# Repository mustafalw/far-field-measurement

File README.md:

# far-field-measurement
This is our EE344 - Electronics Design Lab (EDL) project to build an apparatus for far field measurement of optical sources

A physical apparatus has been designed (a couple of pictures of the same are also there in the repository) to measure the far field angular radiation profile of optical sources like LEDs and laser diodes. The repository contains the comprehensive report, presentation, PCB designs, SPICE designs, LabVIEW codes and the final measurements. In addition, the video demonstrating the working of the apparatus can be found here: https://drive.google.com/open?id=0BwXnf3wcw68YSDE1a096Rm54bTg

Thanks!

Mustafa, Jashan and Deepak

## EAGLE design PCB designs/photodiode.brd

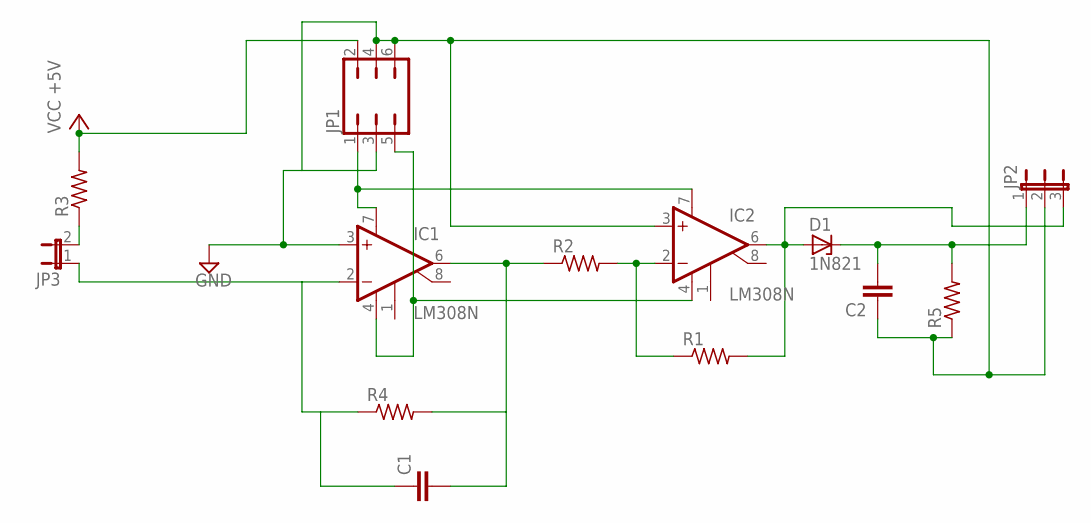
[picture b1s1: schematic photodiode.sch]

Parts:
C1, C2: C-EU025-024X044; C025-024X044
D1: 1N821; DO35Z10
IC1, IC2: LM308N; DIL08
JP1: JP3Q
JP2: JP2E; JP2
JP3: JP1E; JP1
R1, R2, R3, R4, R5: R-US_0207/10; 0207/10

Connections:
GND: C2.1, IC1.3 (+IN), IC2.3 (+IN), JP1.3, JP1.4, JP1.6, JP2.2, R5.1
unnamed: JP3.2, R3.1
unnamed: C1.1, IC1.2 (-IN), JP3.1, R4.1
unnamed: C1.2, IC1.6 (OUT), R2.1, R4.2
unnamed: IC1.7 (V+), IC2.7 (V+), JP1.1
unnamed: D1.A, IC2.6 (OUT), JP2.3, R1.2
unnamed: IC1.4 (V-), IC2.4 (V-), JP1.5
unnamed: C2.2, D1.C, JP2.1, R5.2
unnamed: IC2.2 (-IN), R1.1, R2.2
VCC: JP1.2, R3.2

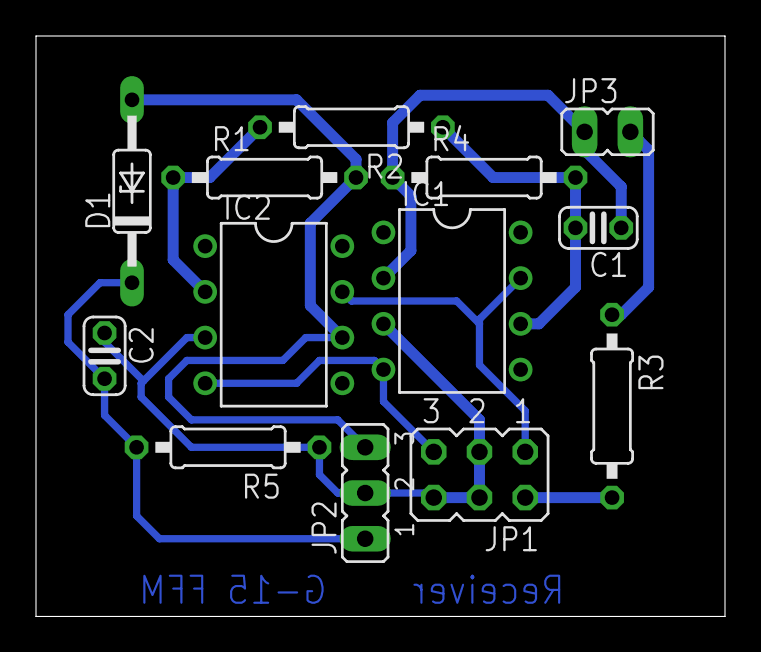
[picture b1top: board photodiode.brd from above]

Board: 2 copper layers, 38.3 x 32.2 mm, 13 parts (0 on the bottom side), 10 nets.

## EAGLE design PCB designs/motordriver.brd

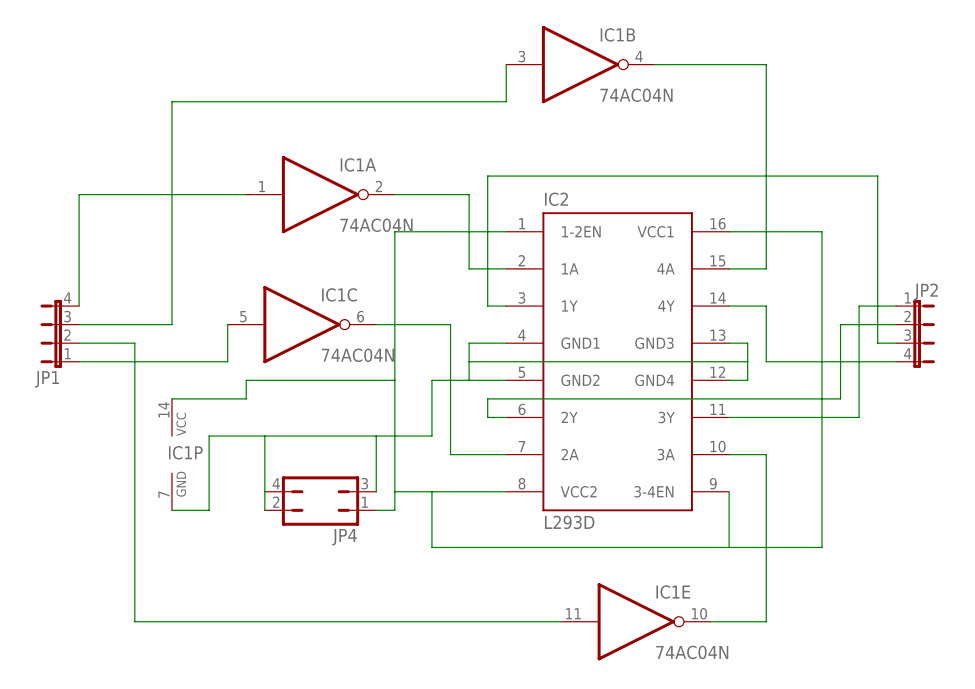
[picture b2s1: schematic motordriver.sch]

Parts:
IC1: 74AC04N; DIL14
IC2: L293D; DIL16
JP1, JP2: JP4E; JP4
JP4: JP2Q

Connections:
unnamed: IC1.1 (I), JP1.4
unnamed: IC1.5 (I), JP1.1
unnamed: IC1.3 (I), JP1.3
unnamed: IC1.2 (O), IC2.2 (1A)
unnamed: IC1.6 (O), IC2.7 (2A)
unnamed: IC1.4 (O), IC2.15 (4A)
unnamed: IC1.10 (O), IC2.10 (3A)
unnamed: IC2.3 (1Y), JP2.3
unnamed: IC2.6 (2Y), JP2.2
unnamed: IC2.11 (3Y), JP2.1
unnamed: IC2.14 (4Y), JP2.4
unnamed: IC1.11 (I), JP1.2
unnamed: IC1.14 (VCC), IC2.1 (1-2EN), IC2.8 (VCC2), IC2.9 (3-4EN), IC2.16 (VCC1), JP4.1
unnamed: IC1.7 (GND), IC2.4 (GND1), IC2.5 (GND2), IC2.12 (GND4), IC2.13 (GND3), JP4.2, JP4.3, JP4.4

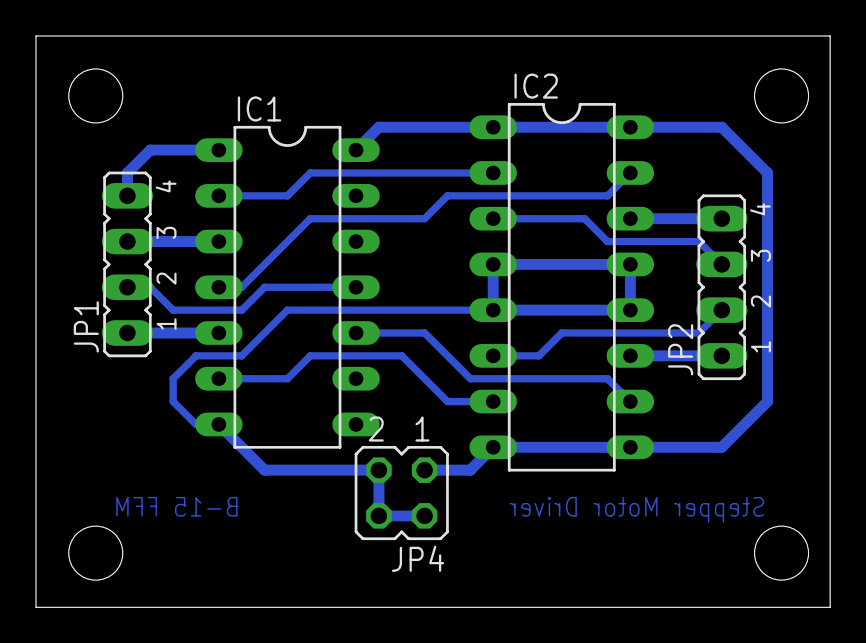
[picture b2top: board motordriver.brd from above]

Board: 2 copper layers, 44.1 x 31.7 mm, 5 parts (0 on the bottom side), 14 nets.

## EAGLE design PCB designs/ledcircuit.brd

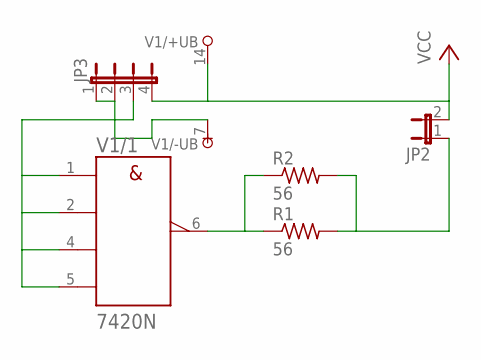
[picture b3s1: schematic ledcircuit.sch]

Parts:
JP2: JP1E; JP1
JP3: JP4E; JP4
R1, R2: 56; 0207/10
V1: 7420N; DIL14

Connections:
unnamed: R1.1, R2.1, V1.6 (Y)
unnamed: JP2.1, R1.2, R2.2
unnamed: JP3.3, V1.1 (A), V1.2 (B), V1.4 (C), V1.5 (D)
unnamed: JP3.1, JP3.2, V1.7 (-UB)
VCC: JP2.2, JP3.4, V1.14 (+UB)

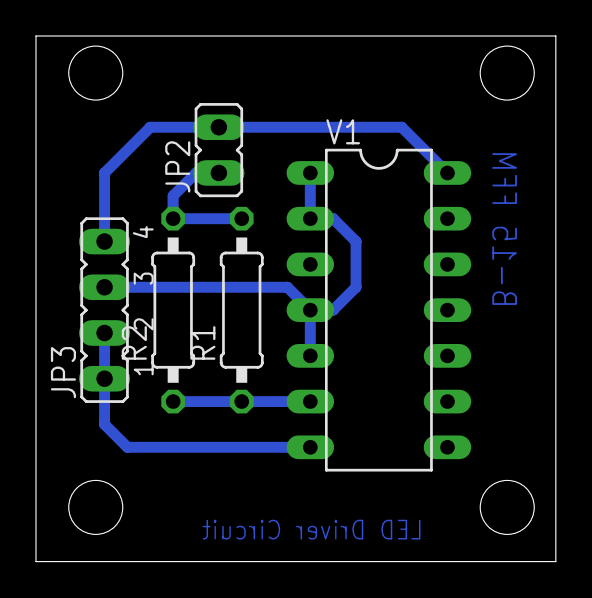
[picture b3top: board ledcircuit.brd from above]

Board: 2 copper layers, 28.9 x 29.2 mm, 5 parts (0 on the bottom side), 5 nets.

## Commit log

2016-05-15 Adding all the relevant files of the project
2016-10-09 Change the possessive determiner from "our'
